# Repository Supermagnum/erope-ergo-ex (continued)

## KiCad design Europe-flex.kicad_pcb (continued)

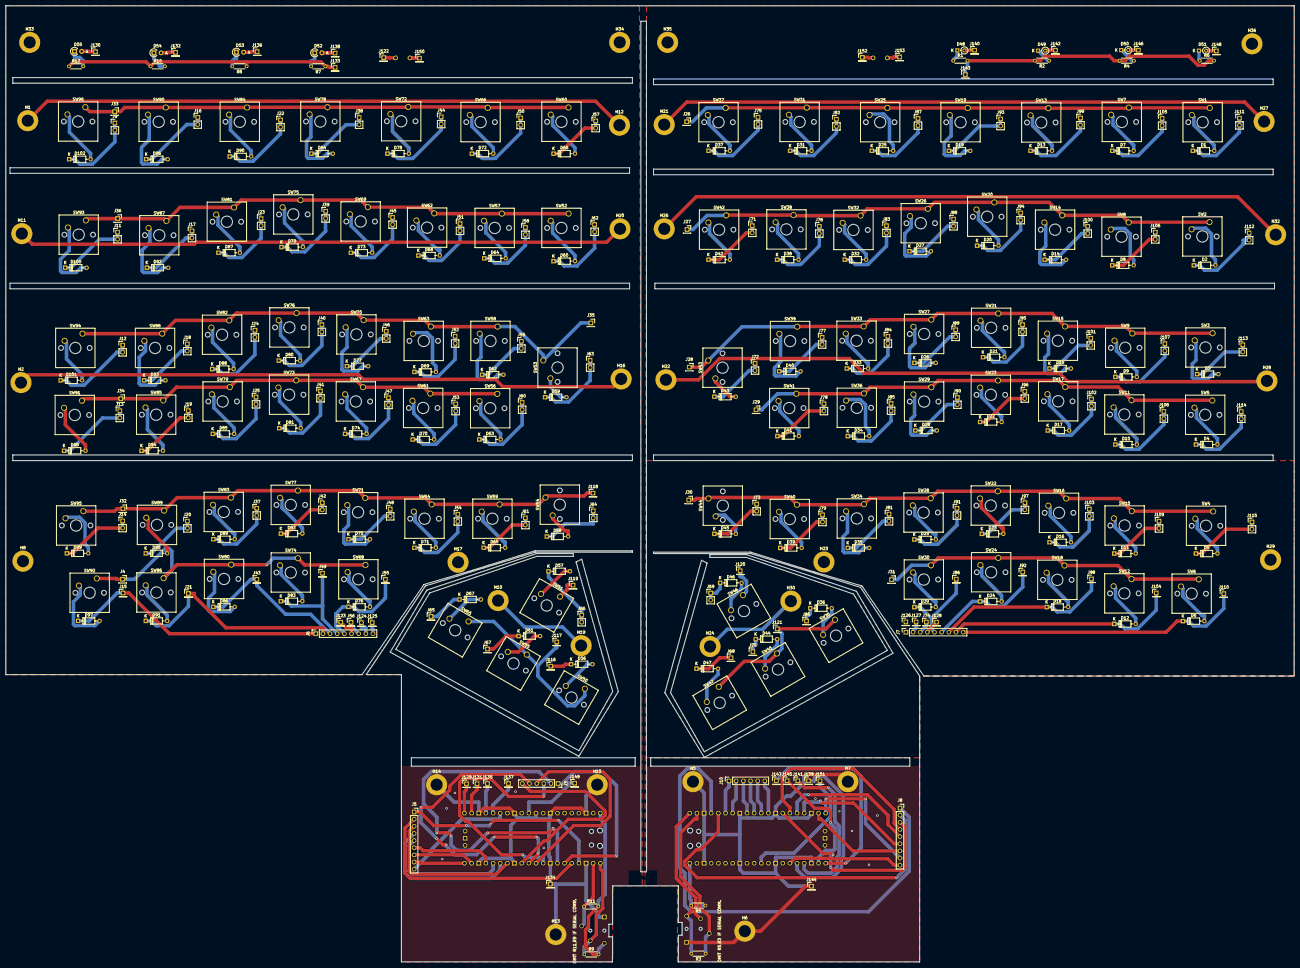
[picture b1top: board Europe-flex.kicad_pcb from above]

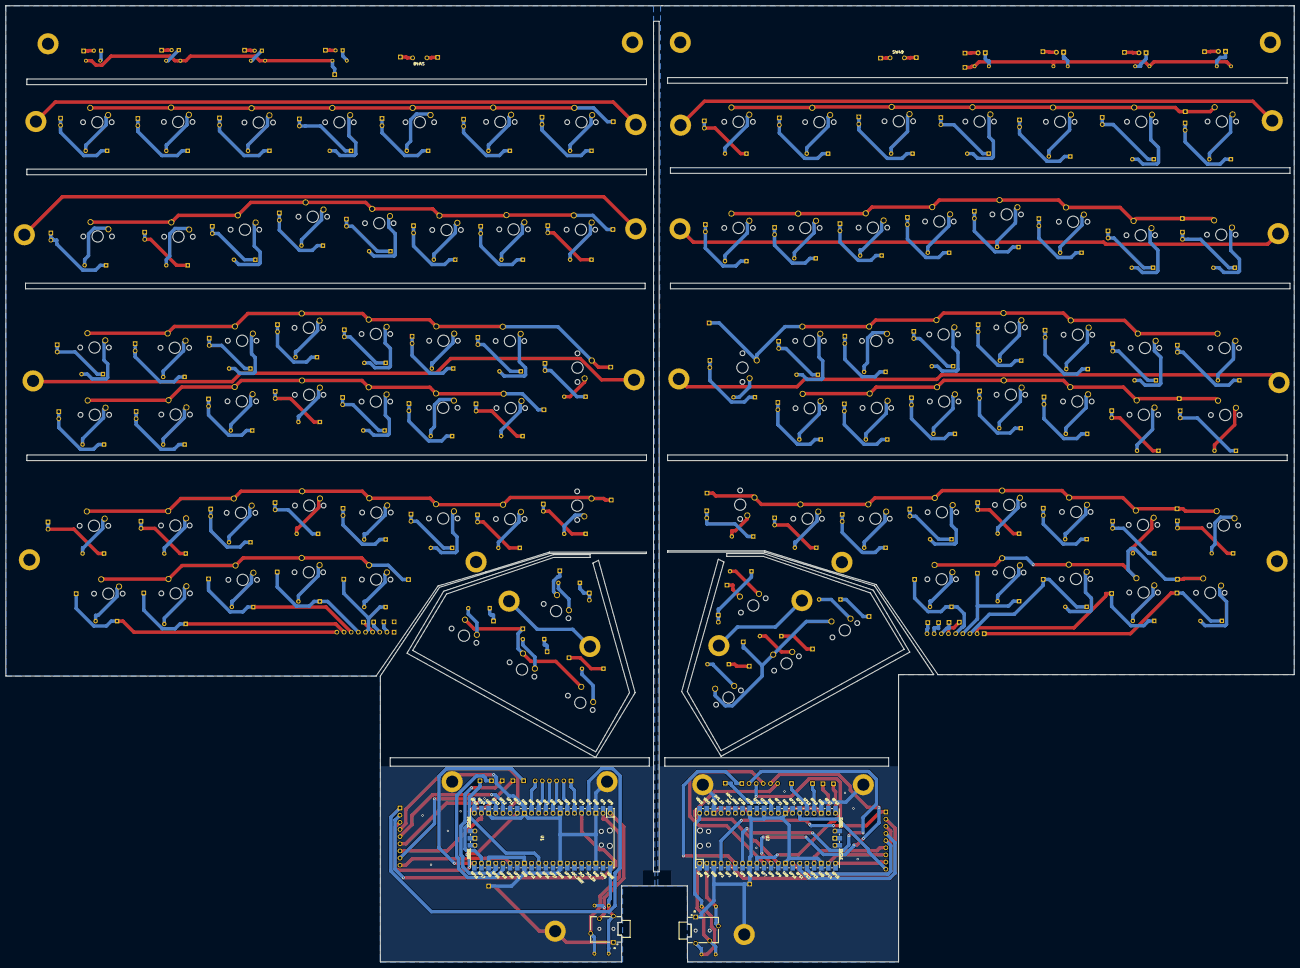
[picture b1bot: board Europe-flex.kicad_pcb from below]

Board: 2 copper layers, 457.5 x 339.5 mm, 395 parts (6 on the bottom side), 294 nets.

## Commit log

2022-12-20 Add files via upload
    added files.
2022-12-24 Add files via upload
    fixed small routing issue
2022-12-25 Update readme.md
    Added todo.
2023-01-02 Add files via upload
    added files for 3D printing.
